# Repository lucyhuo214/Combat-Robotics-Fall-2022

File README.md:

# Combat-Robotics-Fall-2022
Continuation of Combat Robot project using PID control and IMU feedback to enable holonomic drive system in robot.

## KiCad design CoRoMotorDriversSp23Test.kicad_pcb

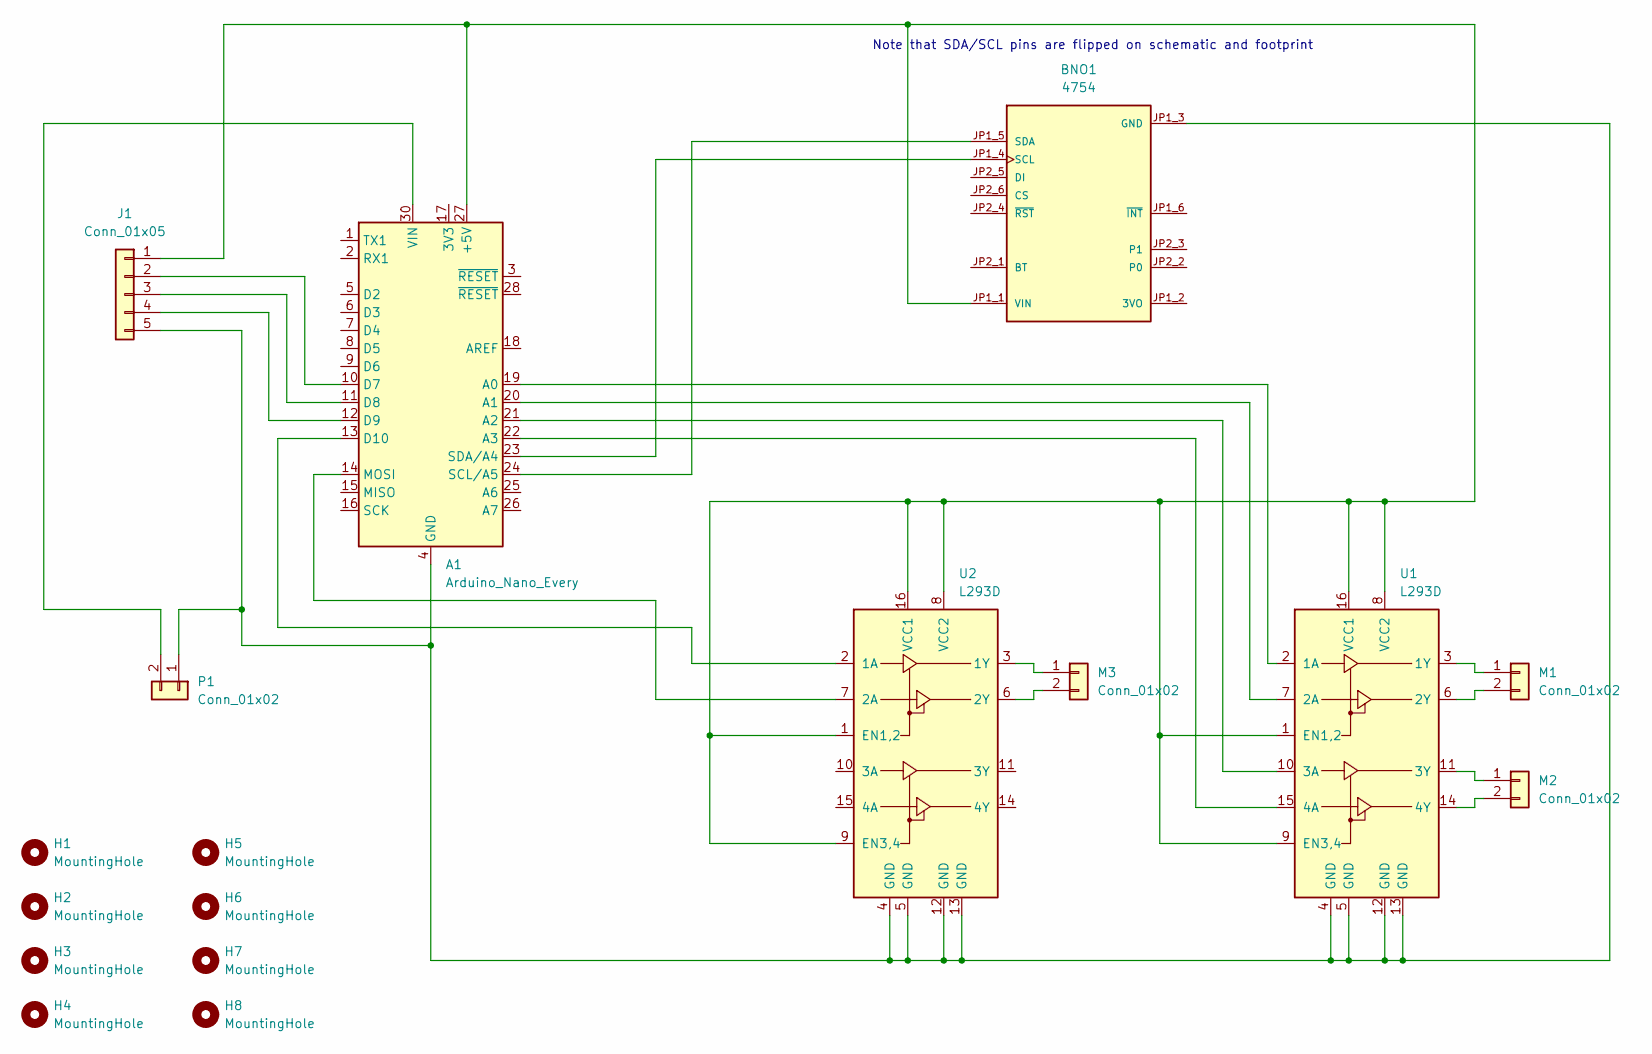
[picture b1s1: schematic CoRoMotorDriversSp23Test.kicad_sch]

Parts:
A1: Arduino_Nano_Every; Arduino_Nano
BNO1: 4754; MODULE_4754; PARTREV 2021-03-16
H1, H2, H3, H4, H5, H6, H7, H8: MountingHole; MountingHole_2.2mm_M2_ISO14580_Pad
J1: Conn_01x05; PinSocket_1x05_P2.54mm_Vertical
M1, M2, M3: Conn_01x02; PinSocket_1x02_P2.54mm_Vertical
P1: Conn_01x02; PinSocket_1x02_P2.54mm_Vertical
U1, U2: L293D; DIP-16_W7.62mm

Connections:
unnamed: A1.10 (D7), J1.2
unnamed: A1.11 (D8), J1.3
unnamed: A1.12 (D9), J1.4
unnamed: A1.13 (D10), U2.2 (1A)
unnamed: A1.14 (MOSI), U2.7 (2A)
unnamed: A1.19 (A0), U1.2 (1A)
unnamed: A1.20 (A1), U1.7 (2A)
unnamed: A1.21 (A2), U1.10 (3A)
unnamed: A1.22 (A3), U1.15 (4A)
unnamed: A1.23 (SDA/A4), BNO1.JP1_4 (SCL)
unnamed: A1.24 (SCL/A5), BNO1.JP1_5 (SDA)
unnamed: A1.27 (+5V), BNO1.JP1_1 (VIN), J1.1, U1.1 (EN1,2), U1.8 (VCC2), U1.9 (EN3,4), U1.16 (VCC1), U2.1 (EN1,2), U2.8 (VCC2), U2.9 (EN3,4), U2.16 (VCC1)
unnamed: A1.4 (GND), A1.29 (GND), BNO1.JP1_3 (GND), J1.5, P1.1, U1.4 (GND), U1.5 (GND), U1.12 (GND), U1.13 (GND), U2.4 (GND), U2.5 (GND), U2.12 (GND), U2.13 (GND)
unnamed: A1.30 (VIN), P1.2
unnamed: M1.1, U1.3 (1Y)
unnamed: M1.2, U1.6 (2Y)
unnamed: M2.1, U1.11 (3Y)
unnamed: M2.2, U1.14 (4Y)
unnamed: M3.1, U2.3 (1Y)
unnamed: M3.2, U2.6 (2Y)

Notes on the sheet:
Note that SDA/SCL pins are flipped on schematic and footprint

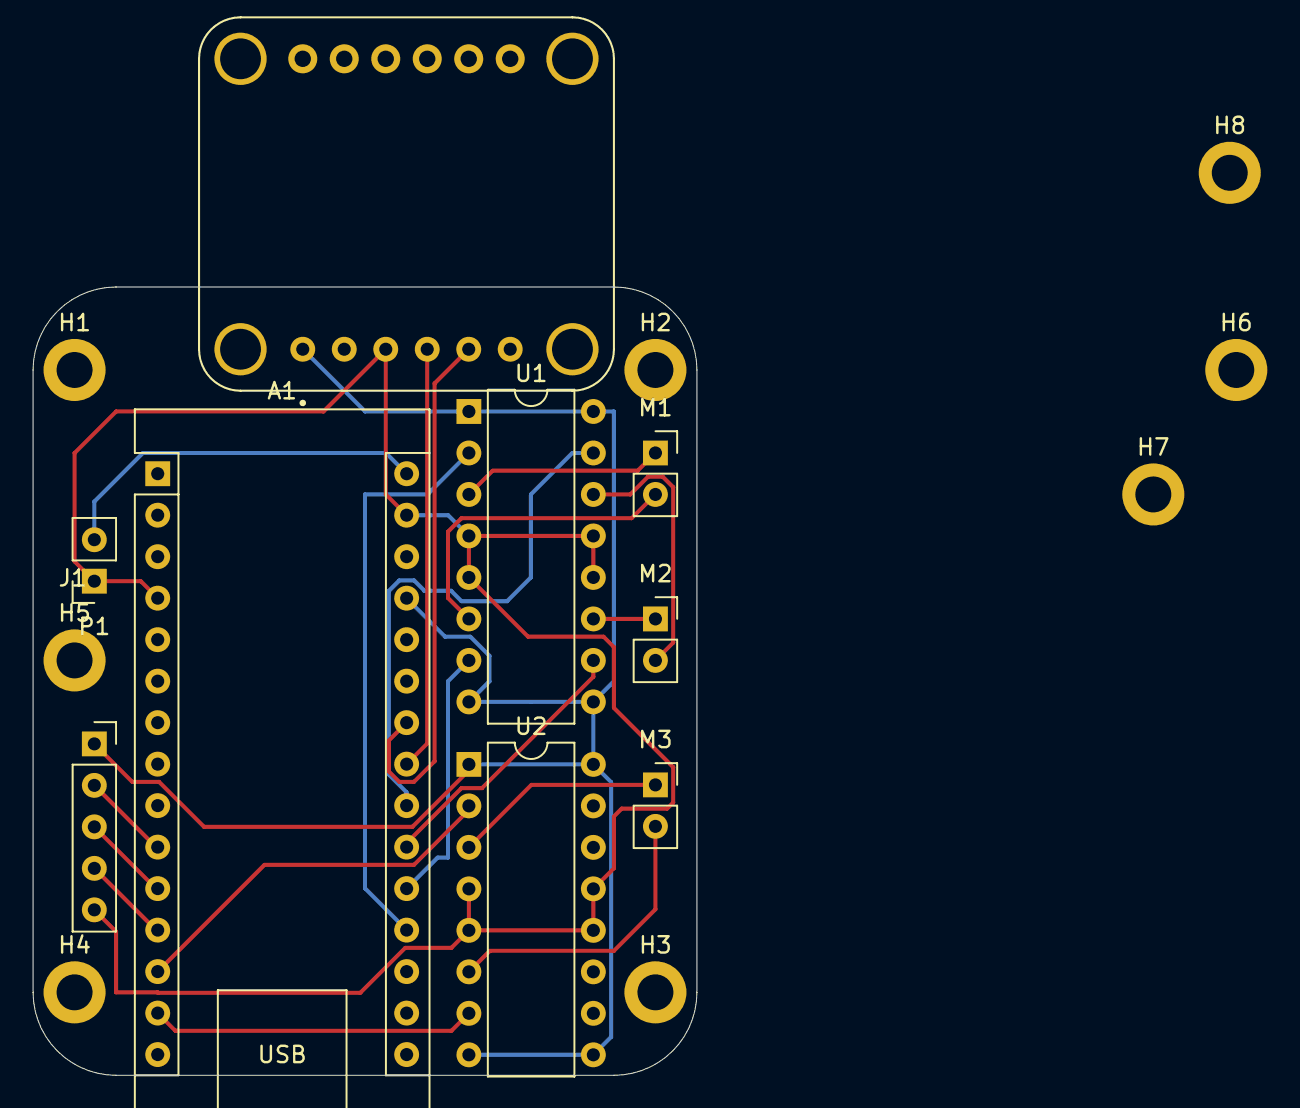
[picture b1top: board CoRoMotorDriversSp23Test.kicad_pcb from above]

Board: 2 copper layers, 40.6 x 48.3 mm, 17 parts (0 on the bottom side), 20 nets.
